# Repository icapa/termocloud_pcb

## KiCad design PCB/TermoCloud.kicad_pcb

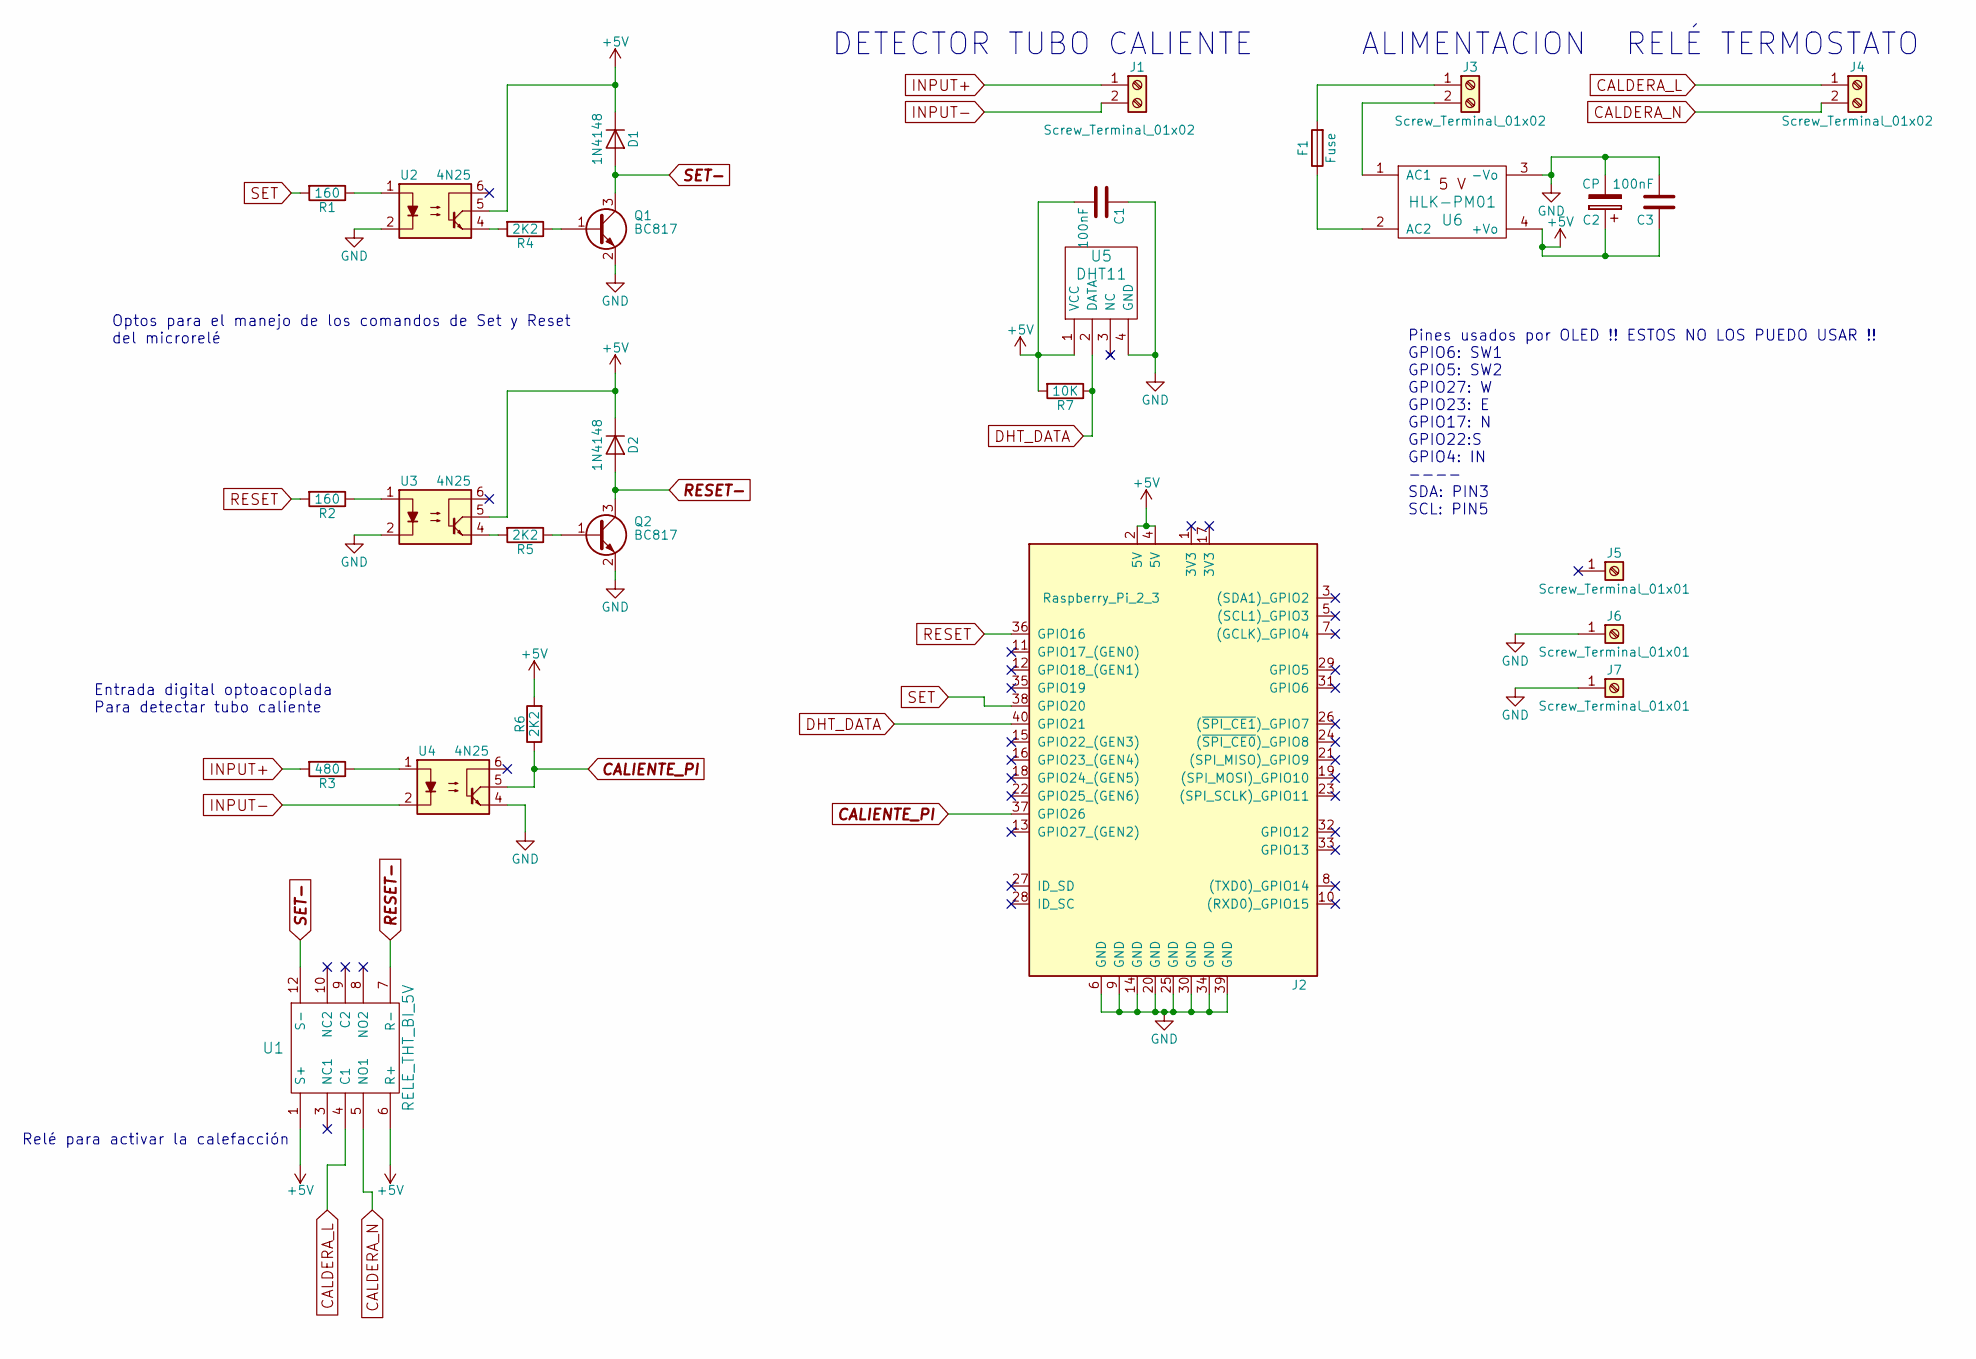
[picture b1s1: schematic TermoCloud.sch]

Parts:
C1: 100nF; C_0603_HandSoldering
C2: CP; CP_Tantalum_Case-A_EIA-3216-18_Reflow
C3: 100nF; C_0603
D1, D2: 1N4148; D_SMB
F1: Fuse; Fuseholder5x20_horiz_SemiClosed_Casing10x25mm
J1, J4: Screw_Terminal_01x02; TerminalBlock_Pheonix_MPT-2.54mm_2pol
J2: Raspberry_Pi_2_3; RPi_Zero
J3: Screw_Terminal_01x02; TerminalBlock_Pheonix_PT-3.5mm_2pol
J5, J6, J7: Screw_Terminal_01x01; 1pin
Q1, Q2: BC817; SOT-23
R1, R2: 160; R_0603
R3: 480; R_0603
R4, R5, R6: 2K2; R_0603
R7: 10K; R_0603
U1: RELE_THT_BI_5V; RELE_THT_2Coin
U2, U3, U4: 4N25; DIP-6_W7.62mm
U5: DHT11; TerminalBlock_Pheonix_MPT-2.54mm_4pol
U6: HLK-PM01

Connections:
+5V: C1.2, C2.1, C3.1, D1.1 (K), D2.1 (K), J2.2 (5V), J2.4 (5V), R6.2, R7.2, U1.1 (S+), U1.6 (R+), U2.5, U3.5, U5.1 (VCC), U6.4 (+Vo)
CALDERA_L: J4.1, U1.4 (C1)
CALDERA_N: J4.2, U1.5 (NO1)
CALIENTE_PI: J2.37 (GPIO26), R6.1, U4.5
DHT_DATA: J2.40 (GPIO21), R7.1, U5.2 (DATA)
GND: C1.1, C2.2, C3.2, J2.6 (GND), J2.9 (GND), J2.14 (GND), J2.20 (GND), J2.25 (GND), J2.30 (GND), J2.34 (GND), J2.39 (GND), J6.1, J7.1, Q1.2 (E), Q2.2 (E), U2.2, U3.2, U4.4, U5.4 (GND), U6.3 (-Vo)
INPUT+: J1.1, R3.2
INPUT-: J1.2, U4.2
unnamed: F1.1, U6.2 (AC2)
unnamed: F1.2, J3.1
unnamed: J3.2, U6.1 (AC1)
unnamed: Q1.1 (B), R4.1
unnamed: Q2.1 (B), R5.1
unnamed: R1.1, U2.1
unnamed: R2.1, U3.1
unnamed: R3.1, U4.1
unnamed: R4.2, U2.4
unnamed: R5.2, U3.4
RESET: J2.36 (GPIO16), R2.2
RESET-: D2.2 (A), Q2.3 (C), U1.7 (R-)
SET: J2.38 (GPIO20), R1.2
SET-: D1.2 (A), Q1.3 (C), U1.12 (S-)

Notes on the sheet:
Optos para el manejo de los comandos de Set y Reset del microrelé
Entrada digital optoacoplada Para detectar tubo caliente
ALIMENTACION
RELÉ TERMOSTATO
DETECTOR TUBO CALIENTE
Pines usados por OLED !! ESTOS NO LOS PUEDO USAR !! GPIO6: SW1 GPIO5: SW2 GPIO27: W GPIO23: E GPIO17: N GPIO22:S GPIO4: IN ---- SDA: PIN3 SCL: PIN5
Relé para activar la calefacción

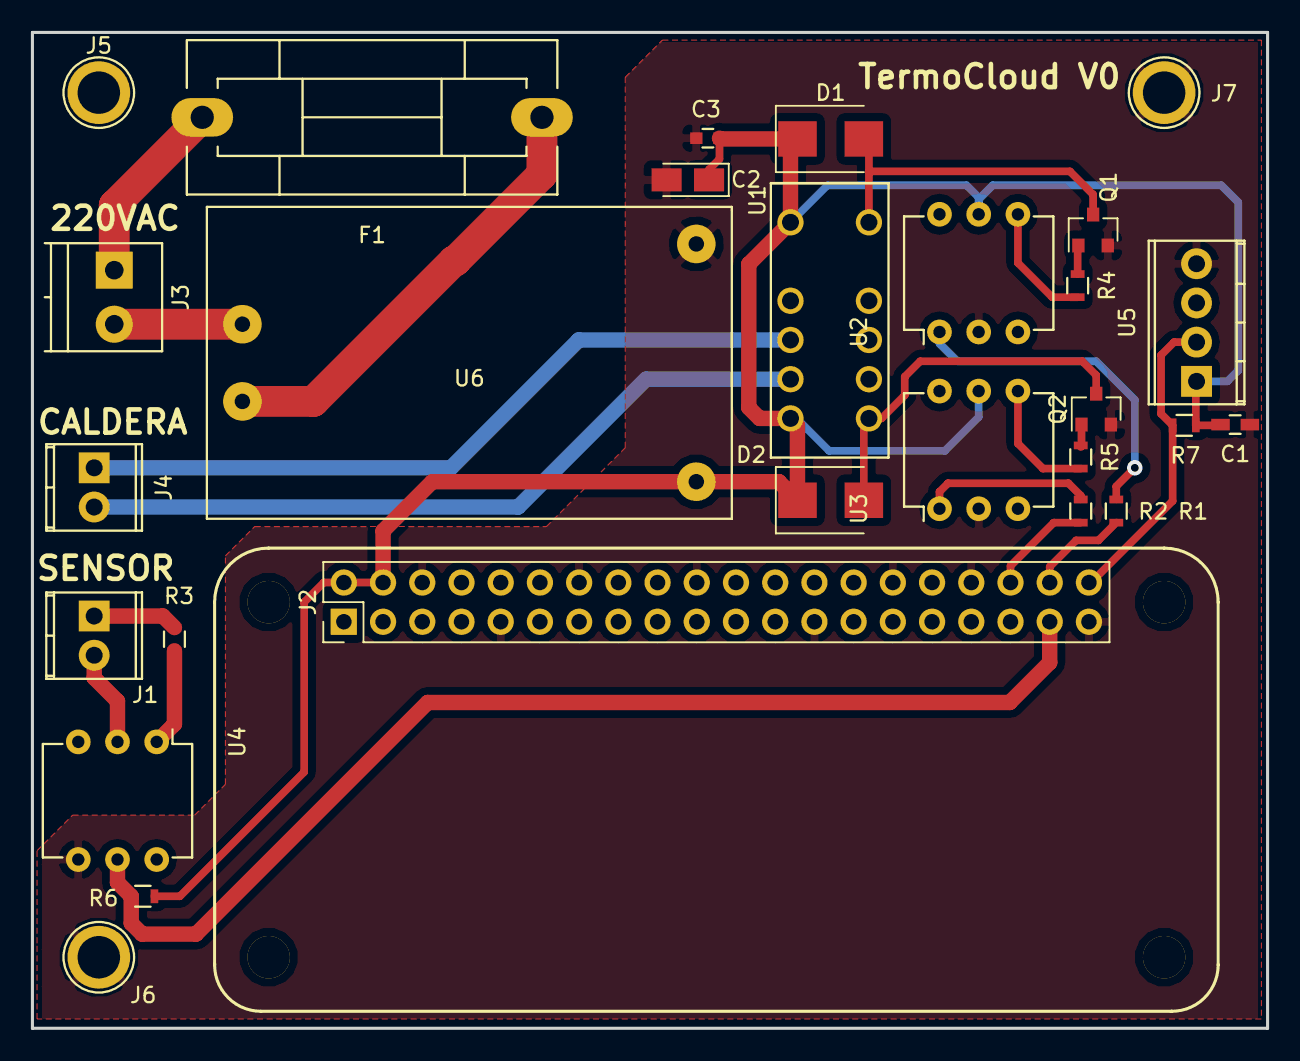
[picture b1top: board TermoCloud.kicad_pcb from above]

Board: 2 copper layers, 80.0 x 64.5 mm, 28 parts (0 on the bottom side), 22 nets.

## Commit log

2018-03-22 First version PCB
2019-01-03 Subo caja mandada a fabricar
2019-01-03 Subo temas de pcb
2019-01-07 Meto la placa que va a la pared
